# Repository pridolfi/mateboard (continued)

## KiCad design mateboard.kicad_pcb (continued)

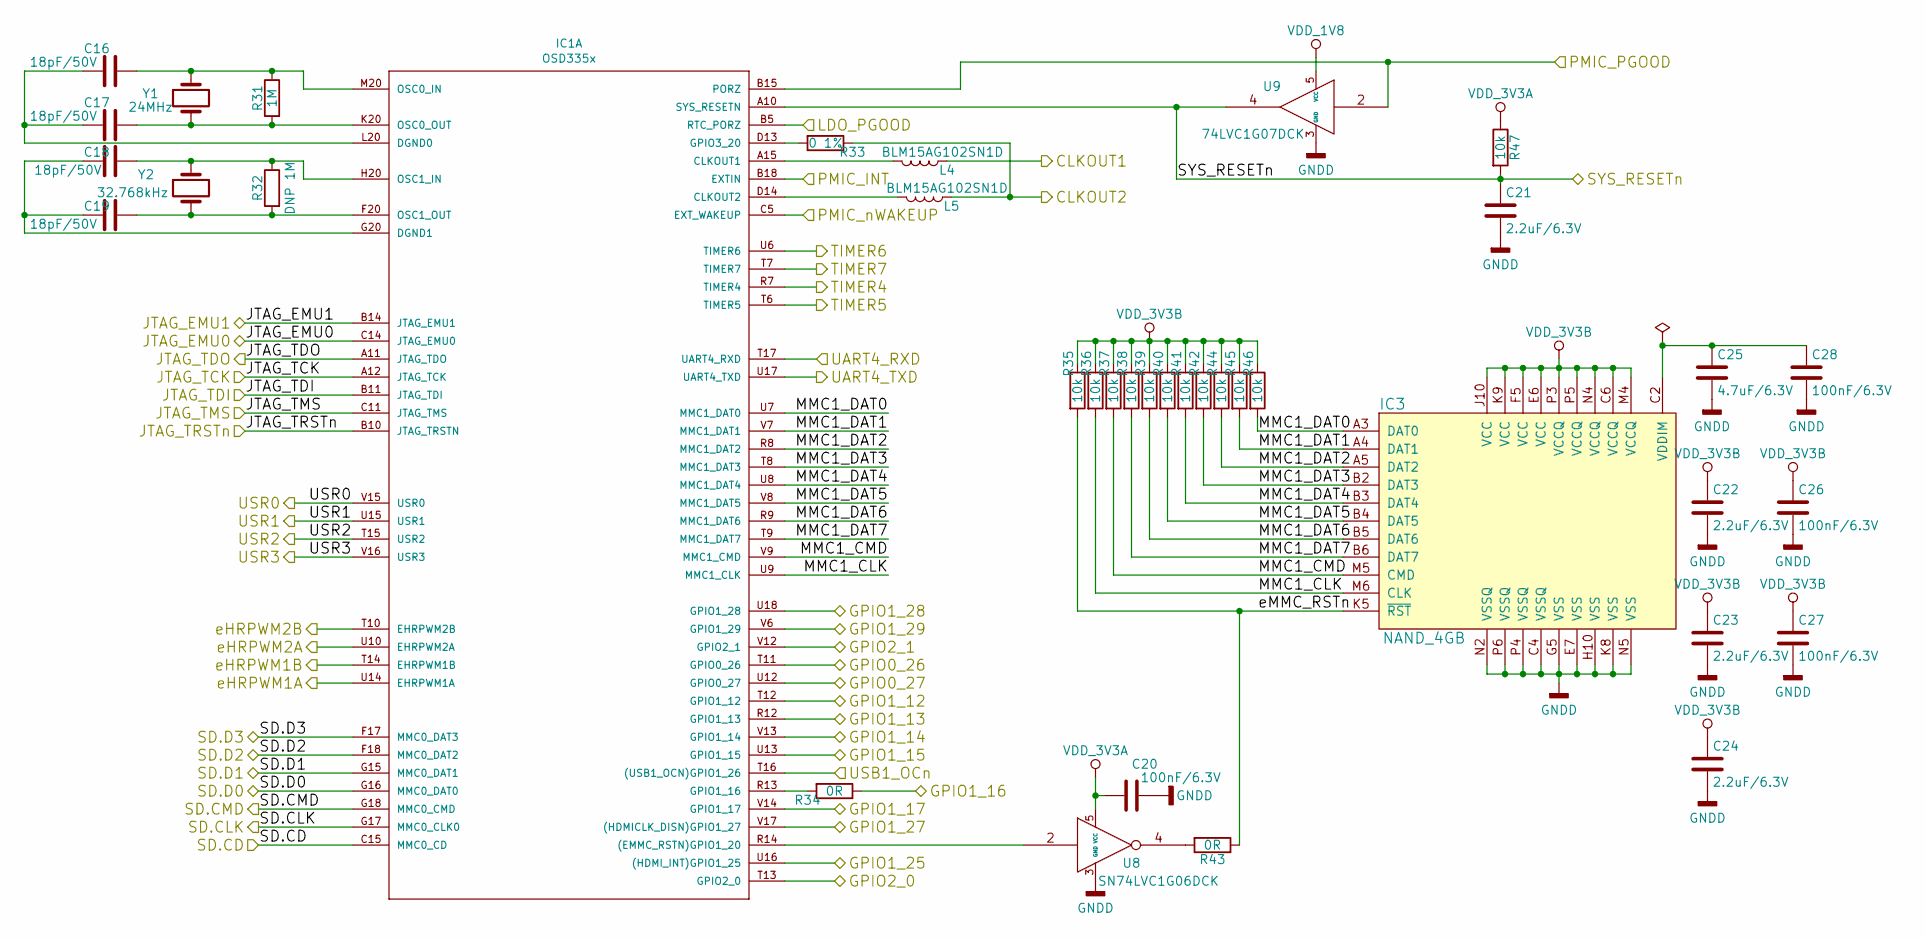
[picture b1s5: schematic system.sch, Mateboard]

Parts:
C16, C17, C18, C19: 18pF/50V; C_0402
C20, C26, C27, C28: 100nF/6.3V; C_0402
C21, C22, C23, C24: 2.2uF/6.3V; C_0603
C25: 4.7uF/6.3V; C_0805
IC1: OSD335x; OSD3358-BAS-BGA400
IC3: NAND_4GB; BeagleBone_Blue-GHI-IC_MICRON_EMMC_153_MODIFICADO
L4, L5: BLM15AG102SN1D; R_0402
R31: 1M; R_0402
R32: DNP 1M; R_0402
R33: 0 1%; R_0402
R34, R43: 0R; R_0402
R35, R36, R37, R38, R39, R40, R41, R42, R44, R45, R46, R47: 10k; R_0402
U8: SN74LVC1G06DCK; SOT-353_SC-70-5
U9: 74LVC1G07DCK; SOT-353_SC-70-5
Y1: 24MHz; Crystal_SMD_5032-2pin_5.0x3.2mm
Y2: 32.768kHz; Crystal_SMD_3215-2pin_3.2x1.5mm

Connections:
/CLKOUT1: L4.1; also elsewhere on the board
/CLKOUT2: L5.1, R33.1; also elsewhere on the board
/GPIO0_26: IC1.T11 (GPIO0_26); also elsewhere on the board
/GPIO0_27: IC1.U12 (GPIO0_27); also elsewhere on the board
/GPIO1_12: IC1.T12 (GPIO1_12); also elsewhere on the board
/GPIO1_13: IC1.R12 (GPIO1_13); also elsewhere on the board
/GPIO1_14: IC1.V13 (GPIO1_14); also elsewhere on the board
/GPIO1_15: IC1.U13 (GPIO1_15); also elsewhere on the board
/GPIO1_16: R34.1; also elsewhere on the board
/GPIO1_17: IC1.V14 (GPIO1_17); also elsewhere on the board
/GPIO1_25: IC1.U16 ((HDMI_INT)GPIO1_25); also elsewhere on the board
/GPIO1_27: IC1.V17 ((HDMICLK_DISN)GPIO1_27); also elsewhere on the board
/GPIO1_28: IC1.U18 (GPIO1_28); also elsewhere on the board
/GPIO1_29: IC1.V6 (GPIO1_29); also elsewhere on the board
/GPIO2_0: IC1.T13 (GPIO2_0); also elsewhere on the board
/GPIO2_1: IC1.V12 (GPIO2_1); also elsewhere on the board
/JTAG_EMU0: IC1.C14 (JTAG_EMU0); also elsewhere on the board
/JTAG_EMU1: IC1.B14 (JTAG_EMU1); also elsewhere on the board
/JTAG_TCK: IC1.A12 (JTAG_TCK); also elsewhere on the board
/JTAG_TDI: IC1.B11 (JTAG_TDI); also elsewhere on the board
/JTAG_TDO: IC1.A11 (JTAG_TDO); also elsewhere on the board
/JTAG_TMS: IC1.C11 (JTAG_TMS); also elsewhere on the board
/JTAG_TRSTn: IC1.B10 (JTAG_TRSTN); also elsewhere on the board
/Power Management/LDO_PGOOD: IC1.B5 (RTC_PORZ); also elsewhere on the board
/Power Management/PMIC_INT: IC1.B18 (EXTIN); also elsewhere on the board
/Power Management/PMIC_PGOOD: IC1.B15 (PORZ), U9.2; also elsewhere on the board
/Power Management/PMIC_nWAKEUP: IC1.C5 (EXT_WAKEUP); also elsewhere on the board
/SD.CD: IC1.C15 (MMC0_CD); also elsewhere on the board
/SD.CLK: IC1.G17 (MMC0_CLK0); also elsewhere on the board
/SD.CMD: IC1.G18 (MMC0_CMD); also elsewhere on the board
/SD.D0: IC1.G16 (MMC0_DAT0); also elsewhere on the board
/SD.D1: IC1.G15 (MMC0_DAT1); also elsewhere on the board
/SD.D2: IC1.F18 (MMC0_DAT2); also elsewhere on the board
/SD.D3: IC1.F17 (MMC0_DAT3); also elsewhere on the board
/SYS_RESETn: C21.1, IC1.A10 (SYS_RESETN), R47.2, U9.4; also elsewhere on the board
/System-eMMC-GPIO/MMC1_CLK: IC1.U9 (MMC1_CLK), IC3.M6 (CLK), R36.2
/System-eMMC-GPIO/MMC1_CMD: IC1.V9 (MMC1_CMD), IC3.M5 (CMD), R37.2
/System-eMMC-GPIO/MMC1_DAT0: IC1.U7 (MMC1_DAT0), IC3.A3 (DAT0), R46.2
/System-eMMC-GPIO/MMC1_DAT1: IC1.V7 (MMC1_DAT1), IC3.A4 (DAT1), R45.2
/System-eMMC-GPIO/MMC1_DAT2: IC1.R8 (MMC1_DAT2), IC3.A5 (DAT2), R44.2
/System-eMMC-GPIO/MMC1_DAT3: IC1.T8 (MMC1_DAT3), IC3.B2 (DAT3), R42.2
/System-eMMC-GPIO/MMC1_DAT4: IC1.U8 (MMC1_DAT4), IC3.B3 (DAT4), R41.2
/System-eMMC-GPIO/MMC1_DAT5: IC1.V8 (MMC1_DAT5), IC3.B4 (DAT5), R40.2
/System-eMMC-GPIO/MMC1_DAT6: IC1.R9 (MMC1_DAT6), IC3.B5 (DAT6), R39.2
/System-eMMC-GPIO/MMC1_DAT7: IC1.T9 (MMC1_DAT7), IC3.B6 (DAT7), R38.2
/System-eMMC-GPIO/USB1_OCn: IC1.T16 ((USB1_OCN)GPIO1_26); also elsewhere on the board
/System-eMMC-GPIO/eMMC_RSTn: IC3.K5 (~RST), R35.2, R43.1
/TIMER4: IC1.R7 (TIMER4); also elsewhere on the board
/TIMER5: IC1.T6 (TIMER5); also elsewhere on the board
/TIMER6: IC1.U6 (TIMER6); also elsewhere on the board
/TIMER7: IC1.T7 (TIMER7); also elsewhere on the board
/UART4_RXD: IC1.T17 (UART4_RXD); also elsewhere on the board
/UART4_TXD: IC1.U17 (UART4_TXD); also elsewhere on the board
/USR0: IC1.V15 (USR0); also elsewhere on the board
/USR1: IC1.U15 (USR1); also elsewhere on the board
/USR2: IC1.T15 (USR2); also elsewhere on the board
/USR3: IC1.V16 (USR3); also elsewhere on the board
/eHRPWM1A: IC1.U14 (EHRPWM1A); also elsewhere on the board
/eHRPWM1B: IC1.T14 (EHRPWM1B); also elsewhere on the board
/eHRPWM2A: IC1.U10 (EHRPWM2A); also elsewhere on the board
/eHRPWM2B: IC1.T10 (EHRPWM2B); also elsewhere on the board
GNDD: C20.2, C21.2, C22.2, C23.2, C24.2, C25.2, C26.2, C27.2, C28.2, IC3.C4 (VSSQ), IC3.E7 (VSS), IC3.G5 (VSS), IC3.H10 (VSS), IC3.K8 (VSS), IC3.N2 (VSSQ), IC3.N5 (VSS), IC3.P4 (VSSQ), IC3.P6 (VSSQ), U8.3 (GND), U9.3 (GND); also elsewhere on the board
unnamed: C16.1, IC1.M20 (OSC0_IN), R31.1, Y1.1
unnamed: C16.2, C17.2, IC1.L20 (DGND0)
unnamed: C17.1, IC1.K20 (OSC0_OUT), R31.2, Y1.2
unnamed: C18.1, IC1.H20 (OSC1_IN), R32.1, Y2.1
unnamed: C18.2, C19.2, IC1.G20 (DGND1)
unnamed: C19.1, IC1.F20 (OSC1_OUT), R32.2, Y2.2
unnamed: C25.1, C28.1, IC3.C2 (VDDIM)
unnamed: IC1.A15 (CLKOUT1), L4.2
unnamed: IC1.D13 (GPIO3_20), R33.2
unnamed: IC1.D14 (CLKOUT2), L5.2
unnamed: IC1.R13 (GPIO1_16), R34.2
unnamed: IC1.R14 ((EMMC_RSTN)GPIO1_20), U8.2
unnamed: R43.2, U8.4
VDD_1V8: U9.5 (VCC); also elsewhere on the board
VDD_3V3A: C20.1, R47.1, U8.5 (VCC); also elsewhere on the board
VDD_3V3B: C22.1, C23.1, C24.1, C26.1, C27.1, IC3.C6 (VCCQ), IC3.E6 (VCC), IC3.F5 (VCC), IC3.J10 (VCC), IC3.K9 (VCC), IC3.M4 (VCCQ), IC3.N4 (VCCQ), IC3.P3 (VCCQ), IC3.P5 (VCCQ), R35.1, R36.1, R37.1, R38.1, R39.1, R40.1, R41.1, R42.1, R44.1, R45.1, R46.1; also elsewhere on the board

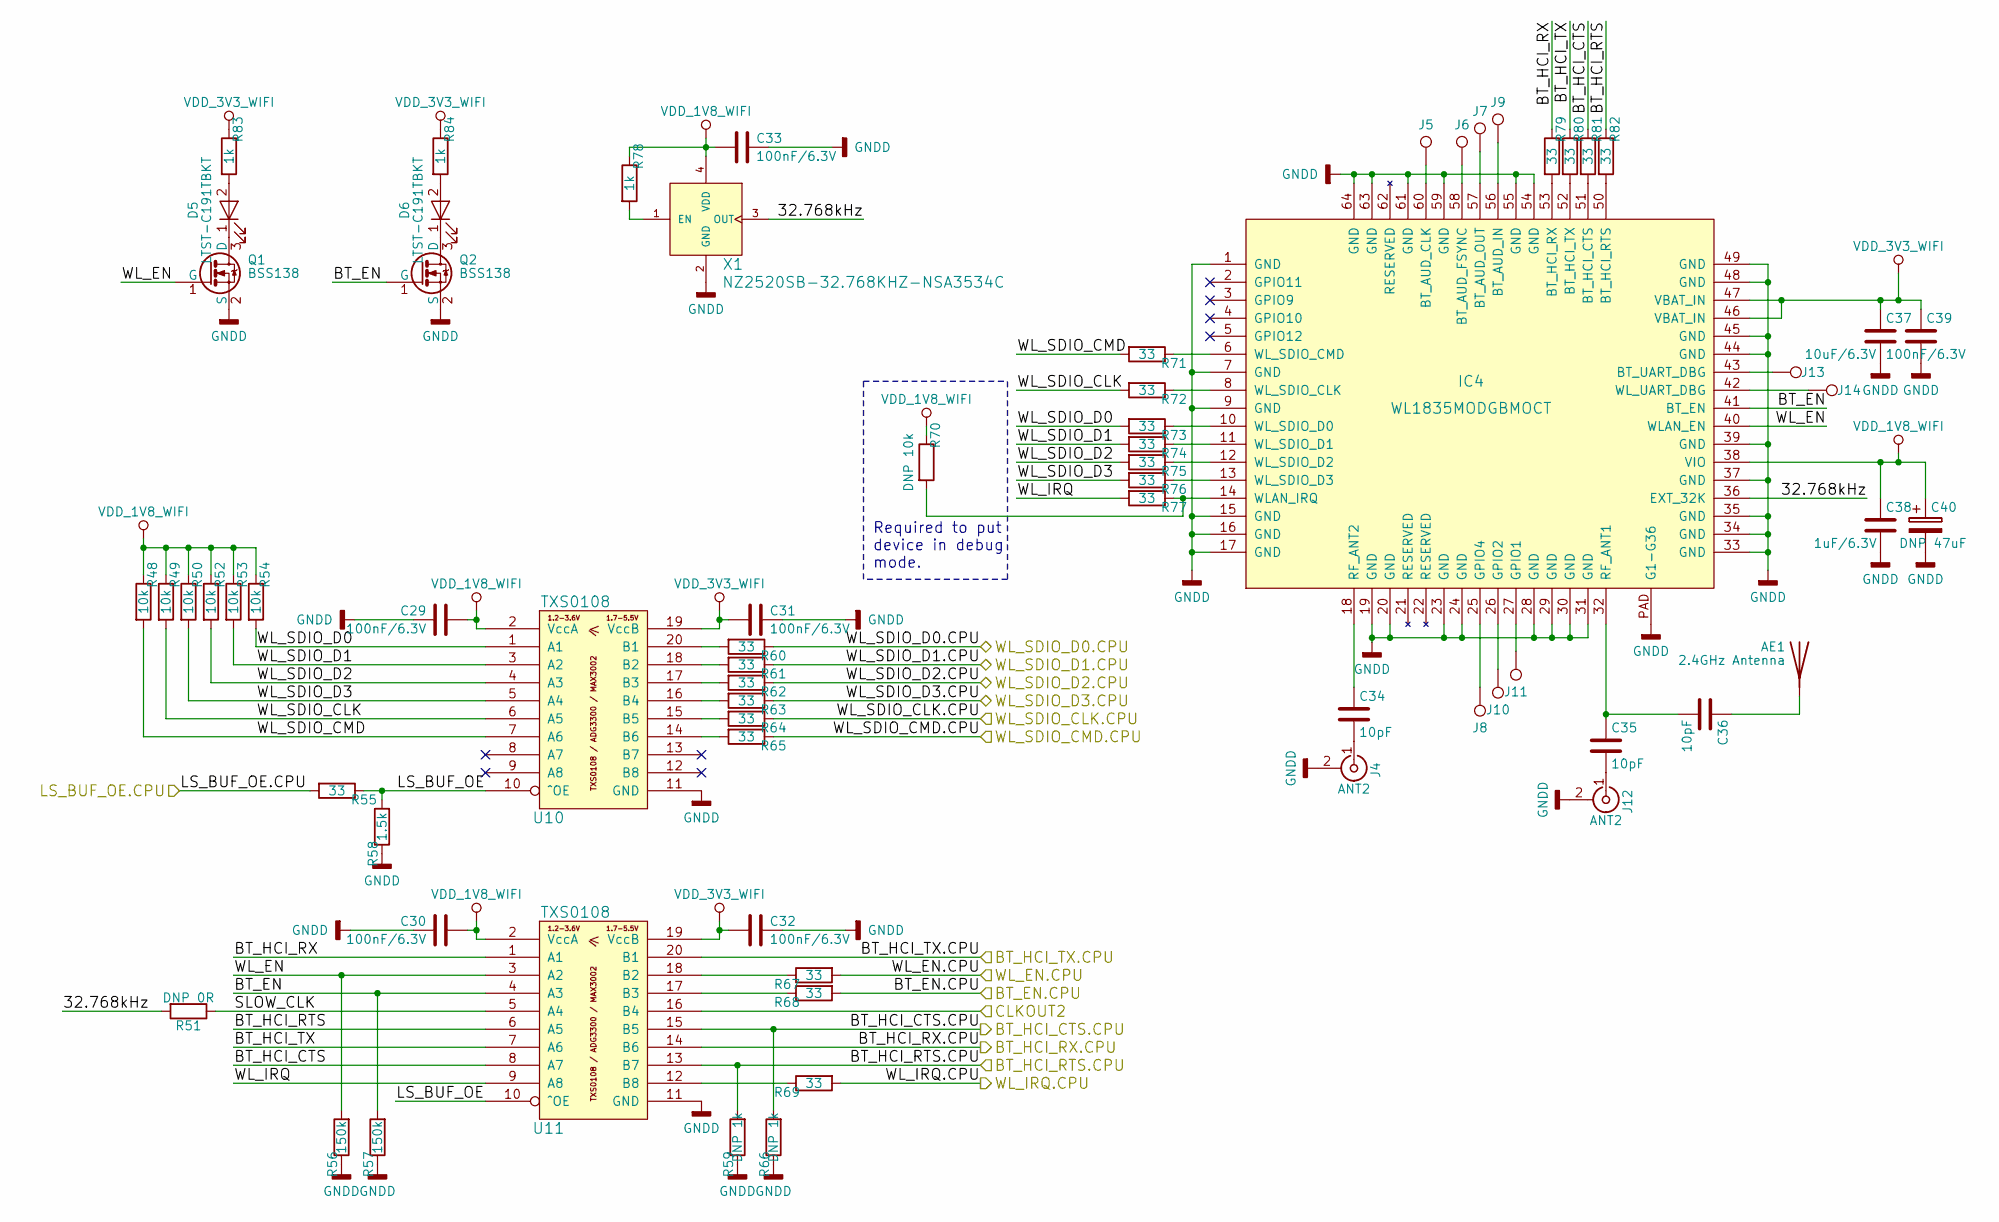
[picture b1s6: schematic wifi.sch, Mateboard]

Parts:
AE1: 2.4GHz Antenna; 2450AT43B100E
C29, C30, C31, C32, C33, C39: 100nF/6.3V; C_0402
C34, C35, C36: 10pF; C_0402
C37: 10uF/6.3V; C_0603
C38: 1uF/6.3V; C_0402
C40: DNP 47uF; CP_Tantalum_Case-A_EIA-3216-18_Reflow
D5, D6: LTST-C191TBKT; LED_0603
IC4: WL1835MODGBMOCT; BeagleBone_Blue-GHI-IC_MOC-100(TI)
J4, J12: ANT2; BeagleBone_Blue-GHI-CONNECTORS_U.FL-R-SMT-1
J5, J6, J7, J8, J9, J10, J11, J13, J14: TEST_1P; Measurement_Point_Round-SMD-Pad_Small
Q1, Q2: BSS138; SOT-23
R48, R49, R50, R52, R53, R54: 10k; R_0402
R51: DNP 0R; R_0402
R55, R60, R61, R62, R63, R64, R65, R67, R68, R69, R71, R72, R73, R74, R75, R76, R77, R79, R80, R81, R82: 33; R_0402
R56, R57: 150k; R_0402
R58: 1.5k; R_0402
R59, R66: DNP 1k; R_0402
R70: DNP 10k; R_0402
R78, R83, R84: 1k; R_0402
U10, U11: TXS0108; TSSOP-20_4.4x6.5mm_Pitch0.65mm
X1: NZ2520SB-32.768KHZ-NSA3534C; Crystal_SMD_2520-4pin_2.5x2.0mm

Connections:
/CLKOUT2: U11.16 (B4); also elsewhere on the board
/Wi-Fi BLE/32.768kHz: IC4.36 (EXT_32K), R51.2, X1.3 (OUT)
/Wi-Fi BLE/BT_EN: IC4.41 (BT_EN), Q2.1 (G), R57.2, U11.4 (A3)
/Wi-Fi BLE/BT_EN.CPU: R68.2; also elsewhere on the board
/Wi-Fi BLE/BT_HCI_CTS: R81.1, U11.8 (A7)
/Wi-Fi BLE/BT_HCI_CTS.CPU: R66.2, U11.15 (B5); also elsewhere on the board
/Wi-Fi BLE/BT_HCI_RTS: R82.1, U11.6 (A5)
/Wi-Fi BLE/BT_HCI_RTS.CPU: R59.2, U11.13 (B7); also elsewhere on the board
/Wi-Fi BLE/BT_HCI_RX: R79.1, U11.1 (A1)
/Wi-Fi BLE/BT_HCI_RX.CPU: U11.14 (B6); also elsewhere on the board
/Wi-Fi BLE/BT_HCI_TX: R80.1, U11.7 (A6)
/Wi-Fi BLE/BT_HCI_TX.CPU: U11.20 (B1); also elsewhere on the board
/Wi-Fi BLE/LS_BUF_OE: R55.1, R58.2, U10.10 (^OE), U11.10 (^OE)
/Wi-Fi BLE/LS_BUF_OE.CPU: R55.2; also elsewhere on the board
/Wi-Fi BLE/SLOW_CLK: R51.1, U11.5 (A4)
/Wi-Fi BLE/WL_EN: IC4.40 (WLAN_EN), Q1.1 (G), R56.2, U11.3 (A2)
/Wi-Fi BLE/WL_EN.CPU: R67.2; also elsewhere on the board
/Wi-Fi BLE/WL_IRQ: R77.2, U11.9 (A8)
/Wi-Fi BLE/WL_IRQ.CPU: R69.2; also elsewhere on the board
/Wi-Fi BLE/WL_SDIO_CLK: R49.2, R72.2, U10.6 (A5)
/Wi-Fi BLE/WL_SDIO_CLK.CPU: R64.1; also elsewhere on the board
/Wi-Fi BLE/WL_SDIO_CMD: R48.2, R71.2, U10.7 (A6)
/Wi-Fi BLE/WL_SDIO_CMD.CPU: R65.1; also elsewhere on the board
/Wi-Fi BLE/WL_SDIO_D0: R54.2, R73.2, U10.1 (A1)
/Wi-Fi BLE/WL_SDIO_D0.CPU: R60.1; also elsewhere on the board
/Wi-Fi BLE/WL_SDIO_D1: R53.2, R74.2, U10.3 (A2)
/Wi-Fi BLE/WL_SDIO_D1.CPU: R61.1; also elsewhere on the board
/Wi-Fi BLE/WL_SDIO_D2: R52.2, R75.2, U10.4 (A3)
/Wi-Fi BLE/WL_SDIO_D2.CPU: R62.1; also elsewhere on the board
/Wi-Fi BLE/WL_SDIO_D3: R50.2, R76.2, U10.5 (A4)
/Wi-Fi BLE/WL_SDIO_D3.CPU: R63.1; also elsewhere on the board
GNDD: C29.1, C30.1, C31.1, C32.1, C33.1, C37.2, C38.2, C39.2, C40.2, IC4.1 (GND), IC4.7 (GND), IC4.9 (GND), IC4.15 (GND), IC4.16 (GND), IC4.17 (GND), IC4.19 (GND), IC4.20 (GND), IC4.23 (GND), IC4.24 (GND), IC4.28 (GND), IC4.29 (GND), IC4.30 (GND), IC4.31 (GND), IC4.33 (GND), IC4.34 (GND), IC4.35 (GND), IC4.37 (GND), IC4.39 (GND), IC4.44 (GND), IC4.45 (GND), IC4.48 (GND), IC4.49 (GND), IC4.54 (GND), IC4.55 (GND), IC4.59 (GND), IC4.61 (GND), IC4.63 (GND), IC4.64 (GND), IC4.PAD (G1-G36), J4.2 (Ext), J12.2 (Ext), Q1.2 (S), Q2.2 (S), R56.1, R57.1, R58.1, R59.1, R66.1, U10.11 (GND), U11.11 (GND), X1.2 (GND); also elsewhere on the board
unnamed: AE1.1, C36.1
unnamed: C34.1, IC4.18 (RF_ANT2)
unnamed: C34.2, J4.1 (In)
unnamed: C35.1, C36.2, IC4.32 (RF_ANT1)
unnamed: C35.2, J12.1 (In)
unnamed: D5.1 (K), Q1.3 (D)
unnamed: D5.2 (A), R83.2
unnamed: D6.1 (K), Q2.3 (D)
unnamed: D6.2 (A), R84.2
unnamed: IC4.6 (WL_SDIO_CMD), R71.1
unnamed: IC4.8 (WL_SDIO_CLK), R72.1
unnamed: IC4.10 (WL_SDIO_D0), R73.1
unnamed: IC4.11 (WL_SDIO_D1), R74.1
unnamed: IC4.12 (WL_SDIO_D2), R75.1
unnamed: IC4.13 (WL_SDIO_D3), R76.1
unnamed: IC4.14 (WLAN_IRQ), R70.2, R77.1
unnamed: IC4.25 (GPIO4), J8.1
unnamed: IC4.26 (GPIO2), J10.1
unnamed: IC4.27 (GPIO1), J11.1
unnamed: IC4.42 (WL_UART_DBG), J14.1
unnamed: IC4.43 (BT_UART_DBG), J13.1
unnamed: IC4.50 (BT_HCI_RTS), R82.2
unnamed: IC4.51 (BT_HCI_CTS), R81.2
unnamed: IC4.52 (BT_HCI_TX), R80.2
unnamed: IC4.53 (BT_HCI_RX), R79.2
unnamed: IC4.56 (BT_AUD_IN), J9.1
unnamed: IC4.57 (BT_AUD_OUT), J7.1
unnamed: IC4.58 (BT_AUD_FSYNC), J6.1
unnamed: IC4.60 (BT_AUD_CLK), J5.1
unnamed: R60.2, U10.20 (B1)
unnamed: R61.2, U10.18 (B2)
unnamed: R62.2, U10.17 (B3)
unnamed: R63.2, U10.16 (B4)
unnamed: R64.2, U10.15 (B5)
unnamed: R65.2, U10.14 (B6)
unnamed: R67.1, U11.18 (B2)
unnamed: R68.1, U11.17 (B3)
unnamed: R69.1, U11.12 (B8)
unnamed: R78.2, X1.1 (EN)
VDD_1V8_WIFI: C29.2, C30.2, C33.2, C38.1, C40.1, IC4.38 (VIO), R48.1, R49.1, R50.1, R52.1, R53.1, R54.1, R70.1, R78.1, U10.2 (VccA), U11.2 (VccA), X1.4 (VDD); also elsewhere on the board
VDD_3V3_WIFI: C31.2, C32.2, C37.1, C39.1, IC4.46 (VBAT_IN), IC4.47 (VBAT_IN), R83.1, R84.1, U10.19 (VccB), U11.19 (VccB); also elsewhere on the board

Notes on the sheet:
Required to put device in debug mode.

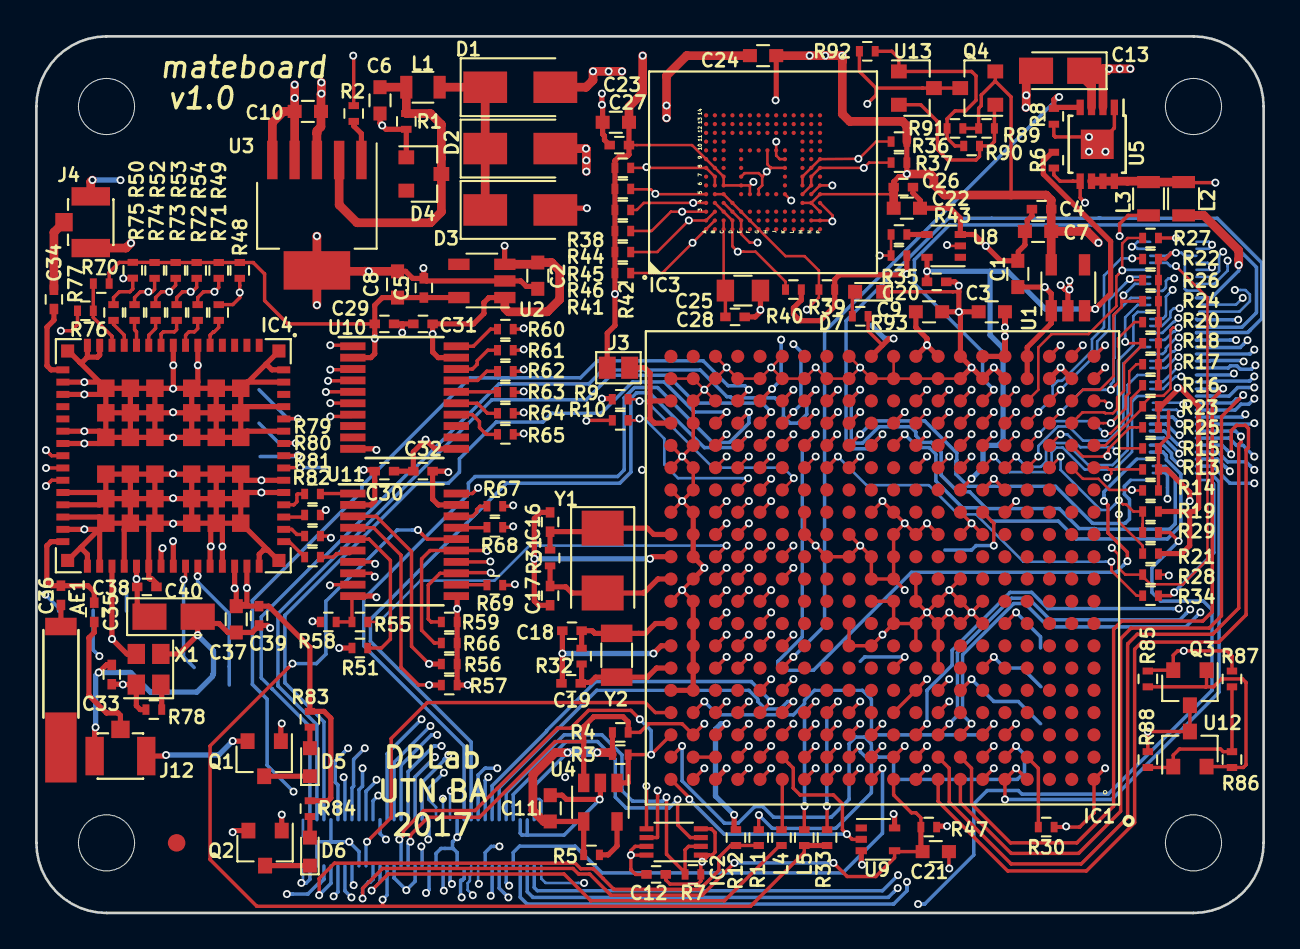
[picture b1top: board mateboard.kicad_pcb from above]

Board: 6 copper layers, 70.0 x 50.0 mm, 190 parts (0 on the bottom side), 239 nets.

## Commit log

2017-02-09 deleted unused libs
2017-02-10 power mgmnt done
2017-02-20 cpu power done
2017-02-21 emmc nand and micro sd
2017-02-21 hierarchical sheets defined
2017-02-23 system sheet
2017-02-23 wip wifi
2017-03-01 wip wl1835 lib
2017-03-02 wifi bt done
2017-03-02 wifi bt leds
2017-03-02 id eeprom
2017-03-02 gpio and boot config
2017-03-02 wip gpio
2017-03-03 gpio assignment done
2017-03-06 gpio connectors
2017-03-08 add doc and update sch
2017-03-08 add logo
2017-03-09 annotation, wip erc
2017-03-10 erc passed, sch first version
2017-03-11 wip display connector
2017-03-16 add display connector, bom generated, sch second version
2017-03-16 wip bom
2017-03-18 wip bom, fix some capacitors
2017-03-18 wip osd335x.lib
2017-03-20 add osd335x documentation
2017-03-20 osd335x lib and kicad_pcb files
2017-03-20 autosave ignored
2017-03-21 wip sch
2017-03-27 wip sys and power
2017-03-28 only io connectors remaining
2017-03-28 wip erc
2017-03-29 erc passed
2017-04-03 bom done
2017-04-04 wip footprint assoc
2017-04-05 start placing
2017-04-05 wip placing
2017-04-10 placing 1st iteration
2017-04-10 G pads of IC4 to GNDD
2017-04-11 footprint check
2017-04-12 wip routing
2017-04-19 wip routing wifi
2017-04-26 connector pinout rearrangement
2017-04-27 arranging signals
2017-04-29 j1 io routing done
2017-04-29 routing j2
2017-04-29 wip j2
2017-05-02 routing done
2017-05-02 routing done, drc ok
2017-05-02 add gerber
2017-05-06 add clamping protection for 3v3a and 3v3b
2017-06-21 sch updated
2017-06-23 logo updated
2017-06-23 footprints updated, add power led
2017-06-23 fixing design
2017-06-23 j1 and j2 aligned, 3d model test
2017-06-29 mateboard v1.0
2017-07-24 gerbers updated, bom using kicost
